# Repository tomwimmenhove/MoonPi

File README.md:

A simple Linux-board with a mini PCIe slot for a 4G LTE module and a 100MBit ethernet port to use as a 4G router.

Specs:
- 100MBit ethernet
- 64MB RAM
- Mini PCIe slot (for an LTE module)
- SD card slot (for firmware)
- SIM card slot
- Allwinner V3S CPU
- 115k2 baud UART console/debugging interface (Optionally over USB)

Thanks to [Dmitry Poskriyakov](https://github.com/balmerdx/AllwinnerV3S_KiCad) for creating the footprints for the used Allwinner V3S CPU.

Multiple kernel versions with working .config files can be found [here](https://github.com/tomwimmenhove/moonpi-linux/).
A U-boot .config is included in [this repository](https://github.com/tomwimmenhove/AllwinnerLTE/blob/main/software/config_notes/uboot.config) and a working version of U-Boot has been forked [here](https://github.com/tomwimmenhove/u-boot).
And finally, ~a working filesystem for the SD-card can be found [here](https://drive.google.com/drive/folders/1GH_1jrhb02dNxiufkJj9f3y94fUZBKtc)~ a working SD-card image with OpenWRT is available [here](https://github.com/tomwimmenhove/MoonPi/blob/main/software/sd_card_image/openwrt.img.gz?raw=true).

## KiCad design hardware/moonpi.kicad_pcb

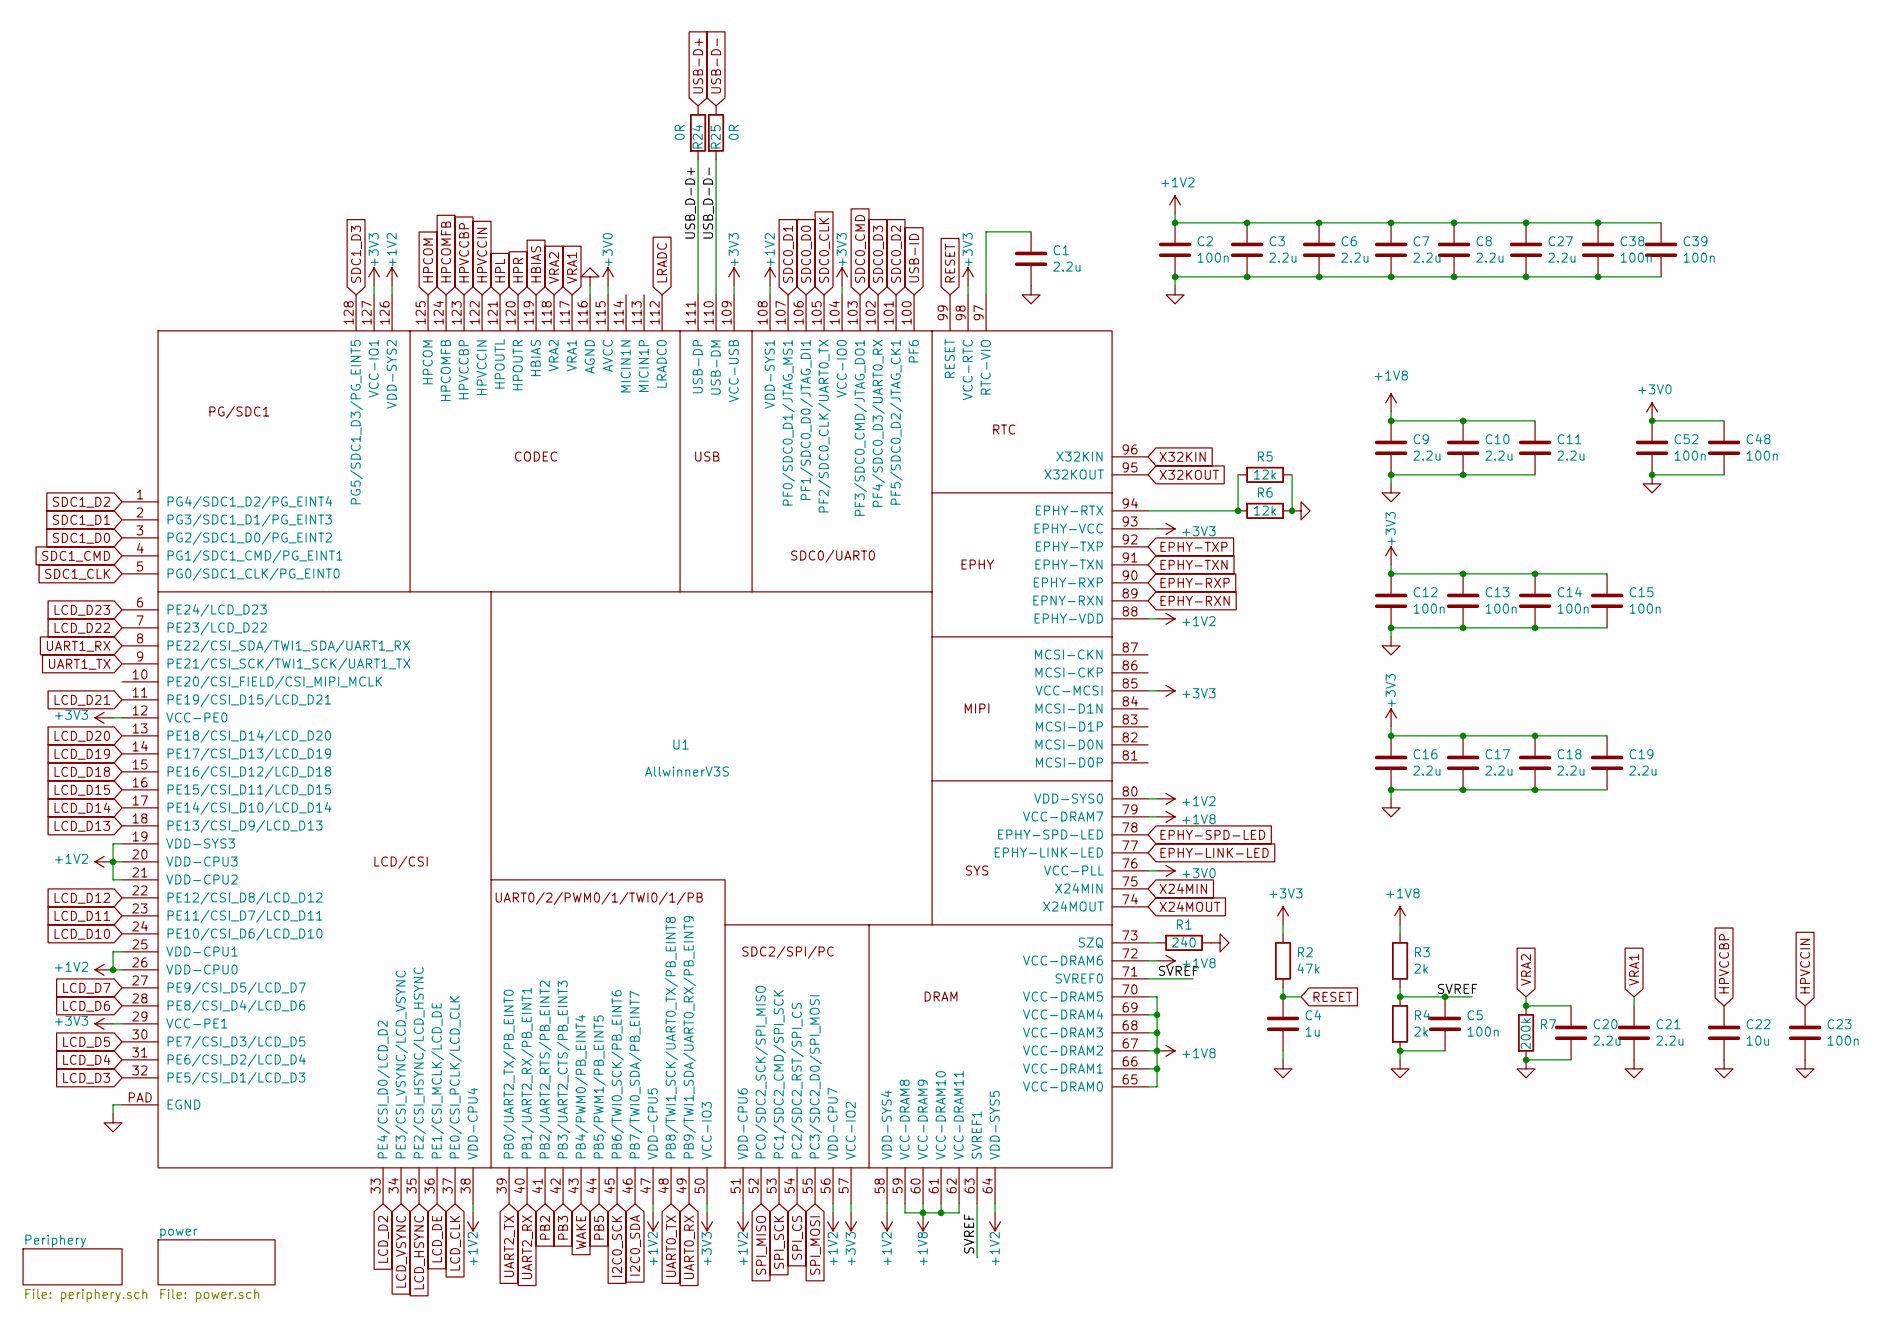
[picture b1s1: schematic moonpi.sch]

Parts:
C1, C3, C6, C7, C8, C9, C10, C11, C16, C17, C18, C19, C20, C21, C27: 2.2u; C_0805_2012Metric
C2, C5, C12, C13, C14, C15, C23, C38, C39, C48, C52: 100n; C_0603_1608Metric
C4: 1u; C_0603_1608Metric
C22: 10u; C_0805_2012Metric
R1: 240; R_0603_1608Metric
R2: 47k; R_0603_1608Metric
R3, R4: 2k; R_0603_1608Metric
R5, R6: 12k; R_0603_1608Metric
R7: 200k; R_0603_1608Metric
R24, R25: 0R; R_0603_1608Metric
U1: AllwinnerV3S; eLQFP-128_14x14mm_P0.4mm

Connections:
+1V2: C2.1, C3.1, C6.1, C7.1, C8.1, C27.1, C38.1, C39.1, U1.19 (VDD-SYS3), U1.20 (VDD-CPU3), U1.21 (VDD-CPU2), U1.25 (VDD-CPU1), U1.26 (VDD-CPU0), U1.38 (VDD-CPU4), U1.47 (VDD-CPU5), U1.51 (VDD-CPU6), U1.56 (VDD-CPU7), U1.58 (VDD-SYS4), U1.64 (VDD-SYS5), U1.80 (VDD-SYS0), U1.88 (EPHY-VDD), U1.108 (VDD-SYS1), U1.126 (VDD-SYS2); also elsewhere on the board
+1V8: C9.1, C10.1, C11.1, R3.1, U1.59 (VCC-DRAM8), U1.60 (VCC-DRAM9), U1.61 (VCC-DRAM10), U1.62 (VCC-DRAM11), U1.65 (VCC-DRAM0), U1.66 (VCC-DRAM1), U1.67 (VCC-DRAM2), U1.68 (VCC-DRAM3), U1.69 (VCC-DRAM4), U1.70 (VCC-DRAM5), U1.72 (VCC-DRAM6), U1.79 (VCC-DRAM7); also elsewhere on the board
+3V0: C48.1, C52.1, U1.76 (VCC-PLL), U1.115 (AVCC); also elsewhere on the board
+3V3: C12.1, C13.1, C14.1, C15.1, C16.1, C17.1, C18.1, C19.1, R2.1, U1.12 (VCC-PE0), U1.29 (VCC-PE1), U1.50 (VCC-IO3), U1.57 (VCC-IO2), U1.85 (VCC-MCSI), U1.93 (EPHY-VCC), U1.98 (VCC-RTC), U1.104 (VCC-IO0), U1.109 (VCC-USB), U1.127 (VCC-IO1); also elsewhere on the board
/SVREF: C5.1, R3.2, R4.1, U1.63 (SVREF1), U1.71 (SVREF0)
/USB_D-D+: R24.2, U1.111 (USB-DP)
/USB_D-D-: R25.2, U1.110 (USB-DM)
EPHY-LINK-LED: U1.77 (EPHY-LINK-LED); also elsewhere on the board
EPHY-RXN: U1.89 (EPNY-RXN); also elsewhere on the board
EPHY-RXP: U1.90 (EPHY-RXP); also elsewhere on the board
EPHY-SPD-LED: U1.78 (EPHY-SPD-LED); also elsewhere on the board
EPHY-TXN: U1.91 (EPHY-TXN); also elsewhere on the board
EPHY-TXP: U1.92 (EPHY-TXP); also elsewhere on the board
GND: C1.2, C2.2, C3.2, C4.2, C5.2, C6.2, C7.2, C8.2, C9.2, C10.2, C11.2, C12.2, C13.2, C14.2, C15.2, C16.2, C17.2, C18.2, C19.2, C20.2, C21.2, C22.2, C23.2, C27.2, C38.2, C39.2, C48.2, C52.2, R1.1, R4.2, R5.1, R6.1, R7.2, U1.116 (AGND), U1.PAD (EGND); also elsewhere on the board
HBIAS: U1.119 (HBIAS)
HPCOM: U1.125 (HPCOM)
HPCOMFB: U1.124 (HPCOMFB)
HPL: U1.121 (HPOUTL)
HPR: U1.120 (HPOUTR)
HPVCCBP: C22.1, U1.123 (HPVCCBP)
HPVCCIN: C23.1, U1.122 (HPVCCIN)
I2C0_SCK: U1.45 (PB6/TWI0_SCK/PB_EINT6)
I2C0_SDA: U1.46 (PB7/TWI0_SDA/PB_EINT7)
LCD_CLK: U1.37 (PE0/CSI_PCLK/LCD_CLK)
LCD_D2: U1.33 (PE4/CSI_D0/LCD_D2)
LCD_D3: U1.32 (PE5/CSI_D1/LCD_D3)
LCD_D4: U1.31 (PE6/CSI_D2/LCD_D4)
LCD_D5: U1.30 (PE7/CSI_D3/LCD_D5)
LCD_D6: U1.28 (PE8/CSI_D4/LCD_D6)
LCD_D7: U1.27 (PE9/CSI_D5/LCD_D7)
LCD_D10: U1.24 (PE10/CSI_D6/LCD_D10)
LCD_D11: U1.23 (PE11/CSI_D7/LCD_D11)
LCD_D12: U1.22 (PE12/CSI_D8/LCD_D12)
LCD_D13: U1.18 (PE13/CSI_D9/LCD_D13)
LCD_D14: U1.17 (PE14/CSI_D10/LCD_D14)
LCD_D15: U1.16 (PE15/CSI_D11/LCD_D15)
LCD_D18: U1.15 (PE16/CSI_D12/LCD_D18)
LCD_D19: U1.14 (PE17/CSI_D13/LCD_D19)
LCD_D20: U1.13 (PE18/CSI_D14/LCD_D20)
LCD_D21: U1.11 (PE19/CSI_D15/LCD_D21)
LCD_D22: U1.7 (PE23/LCD_D22)
LCD_D23: U1.6 (PE24/LCD_D23)
LCD_DE: U1.36 (PE1/CSI_MCLK/LCD_DE)
LCD_HSYNC: U1.35 (PE2/CSI_HSYNC/LCD_HSYNC)
LCD_VSYNC: U1.34 (PE3/CSI_VSYNC/LCD_VSYNC)
LRADC: U1.112 (LRADC0)
unnamed: C1.1, U1.97 (RTC-VIO)
unnamed: R1.2, U1.73 (SZQ)
unnamed: R5.2, R6.2, U1.94 (EPHY-RTX)
PB2: U1.41 (PB2/UART2_RTS/PB_EINT2)
PB3: U1.42 (PB3/UART2_CTS/PB_EINT3)
PB5: U1.44 (PB5/PWM1/PB_EINT5)
RESET: C4.1, R2.2, U1.99 (RESET); also elsewhere on the board
SDC0_CLK: U1.105 (PF2/SDC0_CLK/UART0_TX); also elsewhere on the board
SDC0_CMD: U1.103 (PF3/SDC0_CMD/JTAG_DO1); also elsewhere on the board
SDC0_D0: U1.106 (PF1/SDC0_D0/JTAG_DI1); also elsewhere on the board
SDC0_D1: U1.107 (PF0/SDC0_D1/JTAG_MS1); also elsewhere on the board
SDC0_D2: U1.101 (PF5/SDC0_D2/JTAG_CK1); also elsewhere on the board
SDC0_D3: U1.102 (PF4/SDC0_D3/UART0_RX); also elsewhere on the board
SDC1_CLK: U1.5 (PG0/SDC1_CLK/PG_EINT0); also elsewhere on the board
SDC1_CMD: U1.4 (PG1/SDC1_CMD/PG_EINT1)
SDC1_D0: U1.3 (PG2/SDC1_D0/PG_EINT2)
SDC1_D1: U1.2 (PG3/SDC1_D1/PG_EINT3)
SDC1_D2: U1.1 (PG4/SDC1_D2/PG_EINT4)
SDC1_D3: U1.128 (PG5/SDC1_D3/PG_EINT5)
SPI_CS: U1.54 (PC2/SDC2_RST/SPI_CS); also elsewhere on the board
SPI_MISO: U1.52 (PC0/SDC2_SCK/SPI_MISO); also elsewhere on the board
SPI_MOSI: U1.55 (PC3/SDC2_D0/SPI_MOSI); also elsewhere on the board
SPI_SCK: U1.53 (PC1/SDC2_CMD/SPI_SCK); also elsewhere on the board
UART0_RX: U1.49 (PB9/TWI1_SDA/UART0_RX/PB_EINT9); also elsewhere on the board
UART0_TX: U1.48 (PB8/TWI1_SCK/UART0_TX/PB_EINT8); also elsewhere on the board
UART1_RX: U1.8 (PE22/CSI_SDA/TWI1_SDA/UART1_RX)
UART1_TX: U1.9 (PE21/CSI_SCK/TWI1_SCK/UART1_TX)
UART2_RX: U1.40 (PB1/UART2_RX/PB_EINT1)
UART2_TX: U1.39 (PB0/UART2_TX/PB_EINT0)
USB-D+: R24.1; also elsewhere on the board
USB-D-: R25.1; also elsewhere on the board
USB-ID: U1.100 (PF6); also elsewhere on the board
VRA1: C21.1, U1.117 (VRA1)
VRA2: C20.1, R7.1, U1.118 (VRA2)
WAKE: U1.43 (PB4/PWM0/PB_EINT4); also elsewhere on the board
X24MIN: U1.75 (X24MIN); also elsewhere on the board
X24MOUT: U1.74 (X24MOUT); also elsewhere on the board
X32KIN: U1.96 (X32KIN); also elsewhere on the board
X32KOUT: U1.95 (X32KOUT); also elsewhere on the board

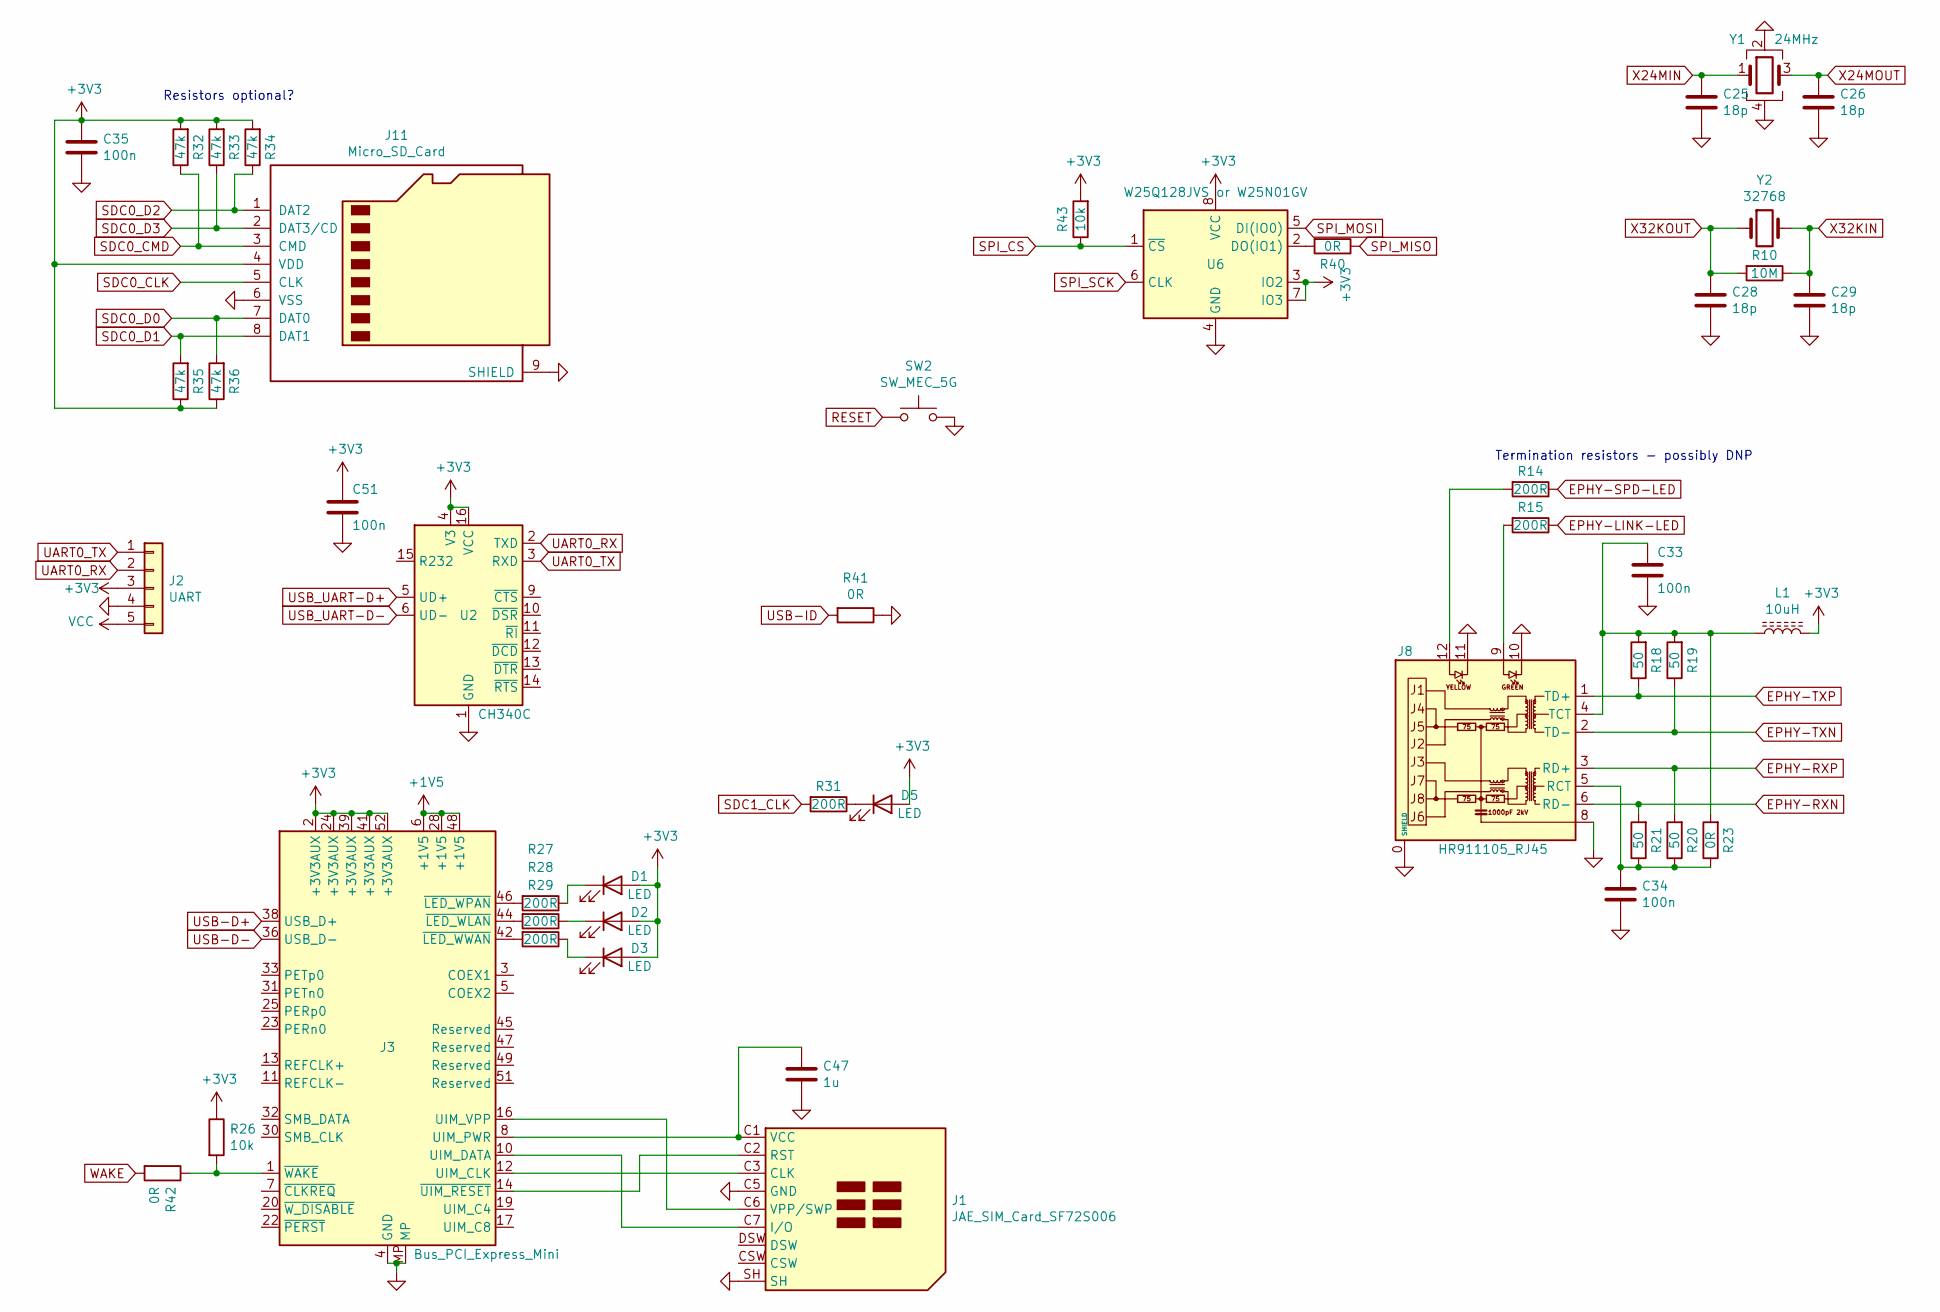
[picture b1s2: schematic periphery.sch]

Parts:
C25, C26, C28, C29: 18p; C_0603_1608Metric
C33, C34, C35, C51: 100n; C_0603_1608Metric
C47: 1u; C_0603_1608Metric
D1, D2, D3, D5: LED; LED_0603_1608Metric
J1: JAE_SIM_Card_SF72S006
J2: UART; PinHeader_1x05_P2.54mm_Vertical
J3: Bus_PCI_Express_Mini; BUS_PCI_Express_Mini_Dual
J8: HR911105_RJ45
J11: Micro_SD_Card; microSD_HC_Wuerth_693072010801
L1: 10uH; L_1206_3216Metric
R10: 10M; R_0805_2012Metric
R14, R15, R27, R28, R29, R31: 200R; R_0603_1608Metric
R18, R19, R20, R21: 50; R_0603_1608Metric
R23, R40, R41, R42: 0R; R_0603_1608Metric
R26, R43: 10k; R_0603_1608Metric
R32, R33, R34, R35, R36: 47k; R_0603_1608Metric
SW2: SW_MEC_5G; SW_SPST_Omron_B3FS-100xP
U2: CH340C; SOIC-16_3.9x9.9mm_P1.27mm
U6: W25Q128JVS or W25N01GV; SOIC-8_5.23x5.23mm_P1.27mm
Y1: 24MHz; Crystal_SMD_3225-4Pin_3.2x2.5mm
Y2: 32768; Crystal_C26-LF_D2.1mm_L6.5mm_Horizontal

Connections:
+1V5: J3.6 (+1V5), J3.28 (+1V5), J3.48 (+1V5); also elsewhere on the board
+3V3: C35.1, C51.1, D1.2 (A), D2.2 (A), D3.2 (A), D5.2 (A), J2.3, J3.2 (+3V3AUX), J3.24 (+3V3AUX), J3.39 (+3V3AUX), J3.41 (+3V3AUX), J3.52 (+3V3AUX), J11.4 (VDD), L1.2, R26.1, R32.2, R33.2, R34.2, R35.1, R36.1, R43.2, U2.4 (V3), U2.16 (VCC), U6.3 (IO2), U6.7 (IO3), U6.8 (VCC); also elsewhere on the board
EPHY-LINK-LED: R15.1; also elsewhere on the board
EPHY-RXN: J8.6 (RD-), R21.2; also elsewhere on the board
EPHY-RXP: J8.3 (RD+), R20.2; also elsewhere on the board
EPHY-SPD-LED: R14.1; also elsewhere on the board
EPHY-TXN: J8.2 (TD-), R19.1; also elsewhere on the board
EPHY-TXP: J8.1 (TD+), R18.1; also elsewhere on the board
GND: C25.2, C26.2, C28.2, C29.2, C33.2, C34.2, C35.2, C47.2, C51.2, J1.C5 (GND), J1.SH, J2.4, J3.4 (GND), J3.9 (GND), J3.15 (GND), J3.18 (GND), J3.21 (GND), J3.26 (GND), J3.27 (GND), J3.29 (GND), J3.34 (GND), J3.35 (GND), J3.37 (GND), J3.40 (GND), J3.43 (GND), J3.50 (GND), J3.MP, J8.0 (SHIELD), J8.8, J8.10, J8.11, J11.6 (VSS), J11.9 (SHIELD), R41.1, SW2.3 (B), SW2.4 (B), U2.1 (GND), U6.4 (GND), Y1.2, Y1.4; also elsewhere on the board
unnamed: C33.1, J8.4 (TCT), L1.1, R18.2, R19.2, R23.2
unnamed: C34.1, J8.5 (RCT), R20.1, R21.1, R23.1
unnamed: C47.1, J1.C1 (VCC), J3.8 (UIM_PWR)
unnamed: D1.1 (K), R27.1
unnamed: D2.1 (K), R28.1
unnamed: D3.1 (K), R29.1
unnamed: D5.1 (K), R31.1
unnamed: J1.C2 (RST), J3.14 (~UIM_RESET)
unnamed: J1.C3 (CLK), J3.12 (UIM_CLK)
unnamed: J1.C6 (VPP/SWP), J3.16 (UIM_VPP)
unnamed: J1.C7 (I/O), J3.10 (UIM_DATA)
unnamed: J3.1 (~WAKE), R26.2, R42.1
unnamed: J3.42 (~LED_WWAN), R29.2
unnamed: J3.44 (~LED_WLAN), R28.2
unnamed: J3.46 (~LED_WPAN), R27.2
unnamed: J8.9, R15.2
unnamed: J8.12, R14.2
unnamed: R40.2, U6.2 (DO(IO1))
RESET: SW2.1 (A), SW2.2 (A); also elsewhere on the board
SDC0_CLK: J11.5 (CLK); also elsewhere on the board
SDC0_CMD: J11.3 (CMD), R32.1; also elsewhere on the board
SDC0_D0: J11.7 (DAT0), R36.2; also elsewhere on the board
SDC0_D1: J11.8 (DAT1), R35.2; also elsewhere on the board
SDC0_D2: J11.1 (DAT2), R34.1; also elsewhere on the board
SDC0_D3: J11.2 (DAT3/CD), R33.1; also elsewhere on the board
SDC1_CLK: R31.2; also elsewhere on the board
SPI_CS: R43.1, U6.1 (~CS); also elsewhere on the board
SPI_MISO: R40.1; also elsewhere on the board
SPI_MOSI: U6.5 (DI(IO0)); also elsewhere on the board
SPI_SCK: U6.6 (CLK); also elsewhere on the board
UART0_RX: J2.2, U2.2 (TXD); also elsewhere on the board
UART0_TX: J2.1, U2.3 (RXD); also elsewhere on the board
USB-D+: J3.38 (USB_D+); also elsewhere on the board
USB-D-: J3.36 (USB_D-); also elsewhere on the board
USB-ID: R41.2; also elsewhere on the board
USB_UART-D+: U2.5 (UD+); also elsewhere on the board
USB_UART-D-: U2.6 (UD-); also elsewhere on the board
VCC: J2.5; also elsewhere on the board
WAKE: R42.2; also elsewhere on the board
X24MIN: C25.1, Y1.1; also elsewhere on the board
X24MOUT: C26.1, Y1.3; also elsewhere on the board
X32KIN: C29.1, R10.1, Y2.2; also elsewhere on the board
X32KOUT: C28.1, R10.2, Y2.1; also elsewhere on the board

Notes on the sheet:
Termination resistors - possibly DNP
Resistors optional?

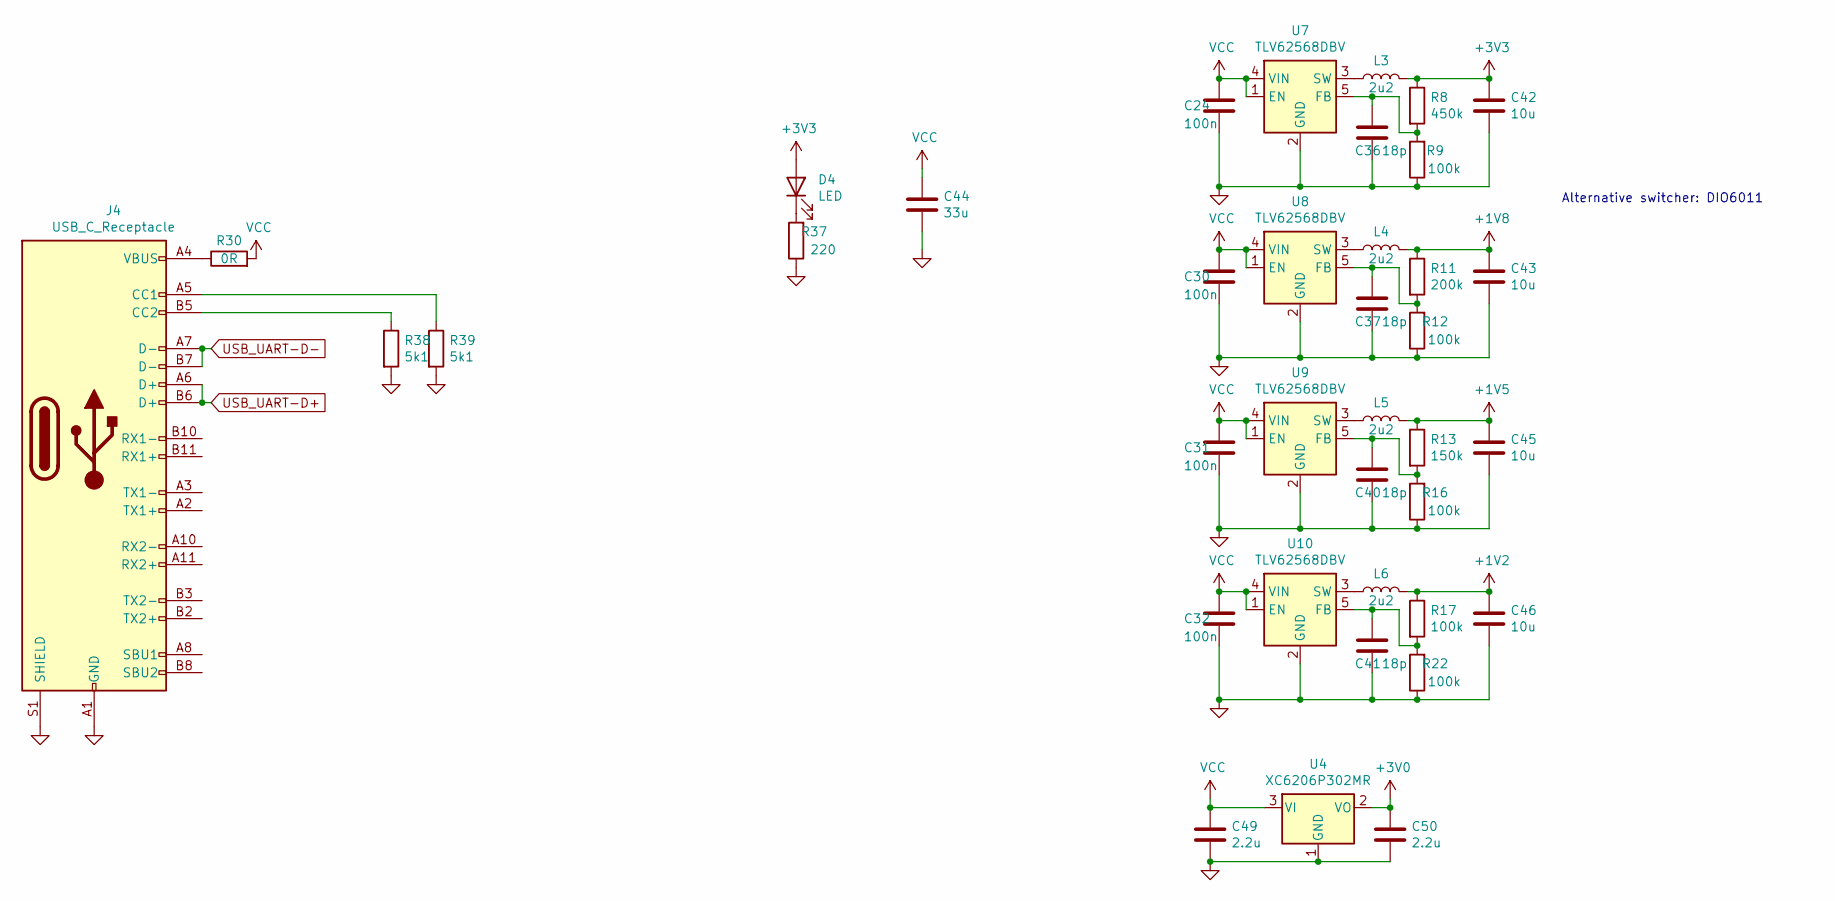
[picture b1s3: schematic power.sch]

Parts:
C24, C30, C31, C32: 100n; C_0603_1608Metric
C36, C37, C40, C41: 18p; C_0603_1608Metric
C42, C43, C45, C46: 10u; C_0805_2012Metric
C44: 33u; C_1206_3216Metric
C49, C50: 2.2u; C_0805_2012Metric
D4: LED; LED_0603_1608Metric
J4: USB_C_Receptacle; USB_C_Receptacle_Amphenol_12401610E4-2A
L3, L4, L5, L6: 2u2; L_TDK_SLF6045
R8: 450k; R_0603_1608Metric
R9, R12, R16, R17, R22: 100k; R_0603_1608Metric
R11: 200k; R_0603_1608Metric
R13: 150k; R_0603_1608Metric
R30: 0R; R_0603_1608Metric
R37: 220; R_0603_1608Metric
R38, R39: 5k1; R_0603_1608Metric
U4: XC6206P302MR; SOT-23
U7, U8, U9, U10: TLV62568DBV; SOT-23-5

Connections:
+1V2: C46.1, L6.2, R17.1; also elsewhere on the board
+1V5: C45.1, L5.2, R13.1; also elsewhere on the board
+1V8: C43.1, L4.2, R11.1; also elsewhere on the board
+3V0: C50.1, U4.2 (VO); also elsewhere on the board
+3V3: C42.1, D4.2 (A), L3.2, R8.1; also elsewhere on the board
GND: C24.2, C30.2, C31.2, C32.2, C36.2, C37.2, C40.2, C41.2, C42.2, C43.2, C44.2, C45.2, C46.2, C49.2, C50.2, J4.A1 (GND), J4.A12 (GND), J4.B1 (GND), J4.B12 (GND), J4.S1 (SHIELD), R9.1, R12.1, R16.1, R22.1, R37.1, R38.2, R39.2, U4.1 (GND), U7.2 (GND), U8.2 (GND), U9.2 (GND), U10.2 (GND); also elsewhere on the board
unnamed: C36.1, R8.2, R9.2, U7.5 (FB)
unnamed: C37.1, R11.2, R12.2, U8.5 (FB)
unnamed: C40.1, R13.2, R16.2, U9.5 (FB)
unnamed: C41.1, R17.2, R22.2, U10.5 (FB)
unnamed: D4.1 (K), R37.2
unnamed: J4.A4 (VBUS), J4.A9 (VBUS), J4.B4 (VBUS), J4.B9 (VBUS), R30.1
unnamed: J4.A5 (CC1), R39.1
unnamed: J4.B5 (CC2), R38.1
unnamed: L3.1, U7.3 (SW)
unnamed: L4.1, U8.3 (SW)
unnamed: L5.1, U9.3 (SW)
unnamed: L6.1, U10.3 (SW)
USB_UART-D+: J4.A6 (D+), J4.B6 (D+); also elsewhere on the board
USB_UART-D-: J4.A7 (D-), J4.B7 (D-); also elsewhere on the board
VCC: C24.1, C30.1, C31.1, C32.1, C44.1, C49.1, R30.2, U4.3 (VI), U7.1 (EN), U7.4 (VIN), U8.1 (EN), U8.4 (VIN), U9.1 (EN), U9.4 (VIN), U10.1 (EN), U10.4 (VIN); also elsewhere on the board

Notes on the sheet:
Alternative switcher: DIO6011

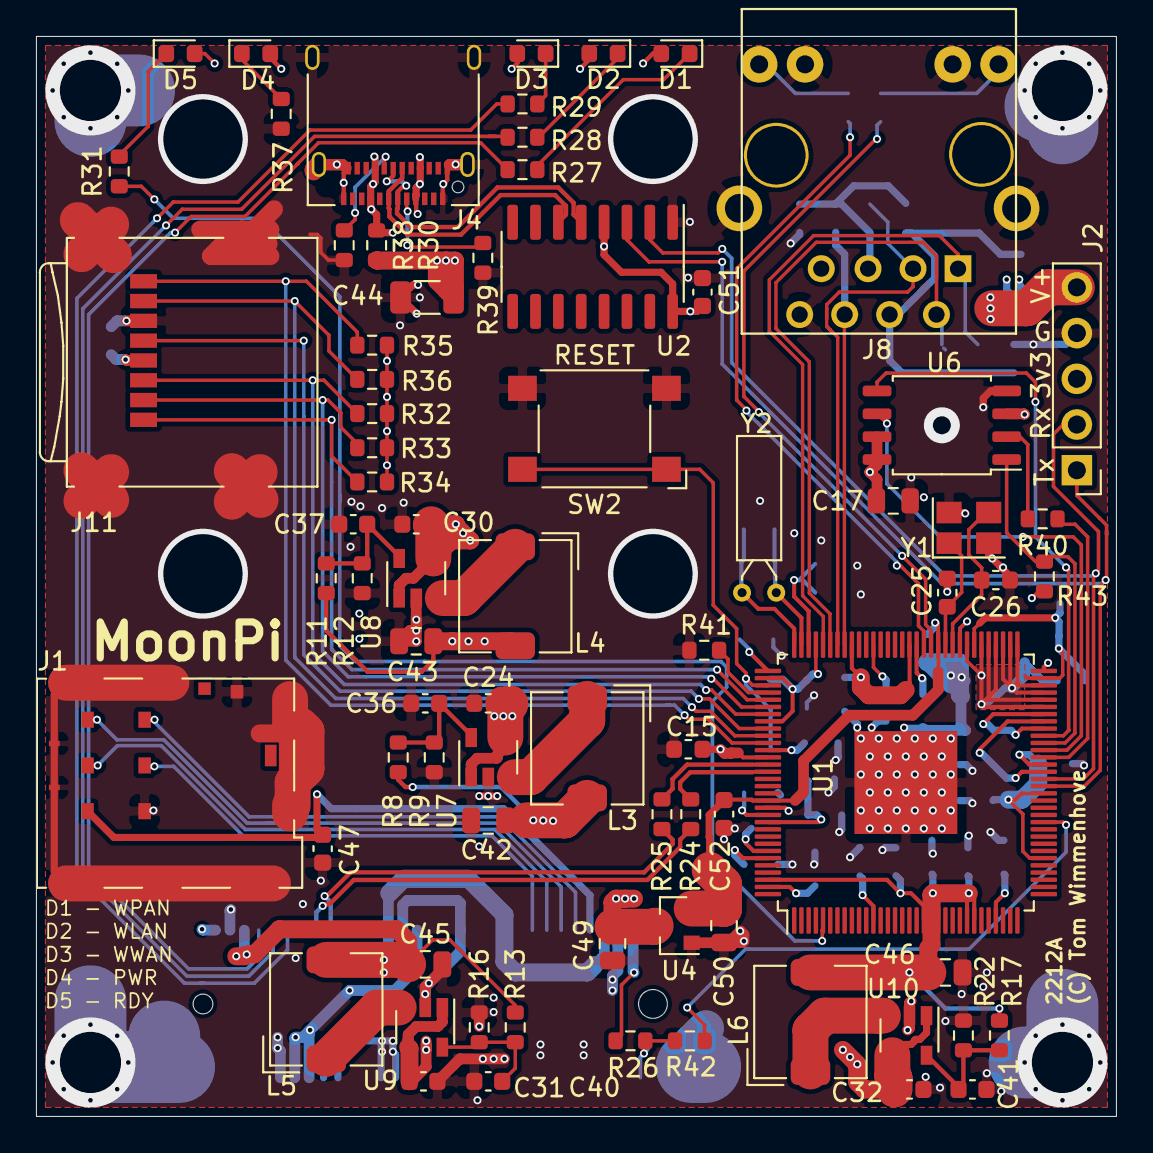
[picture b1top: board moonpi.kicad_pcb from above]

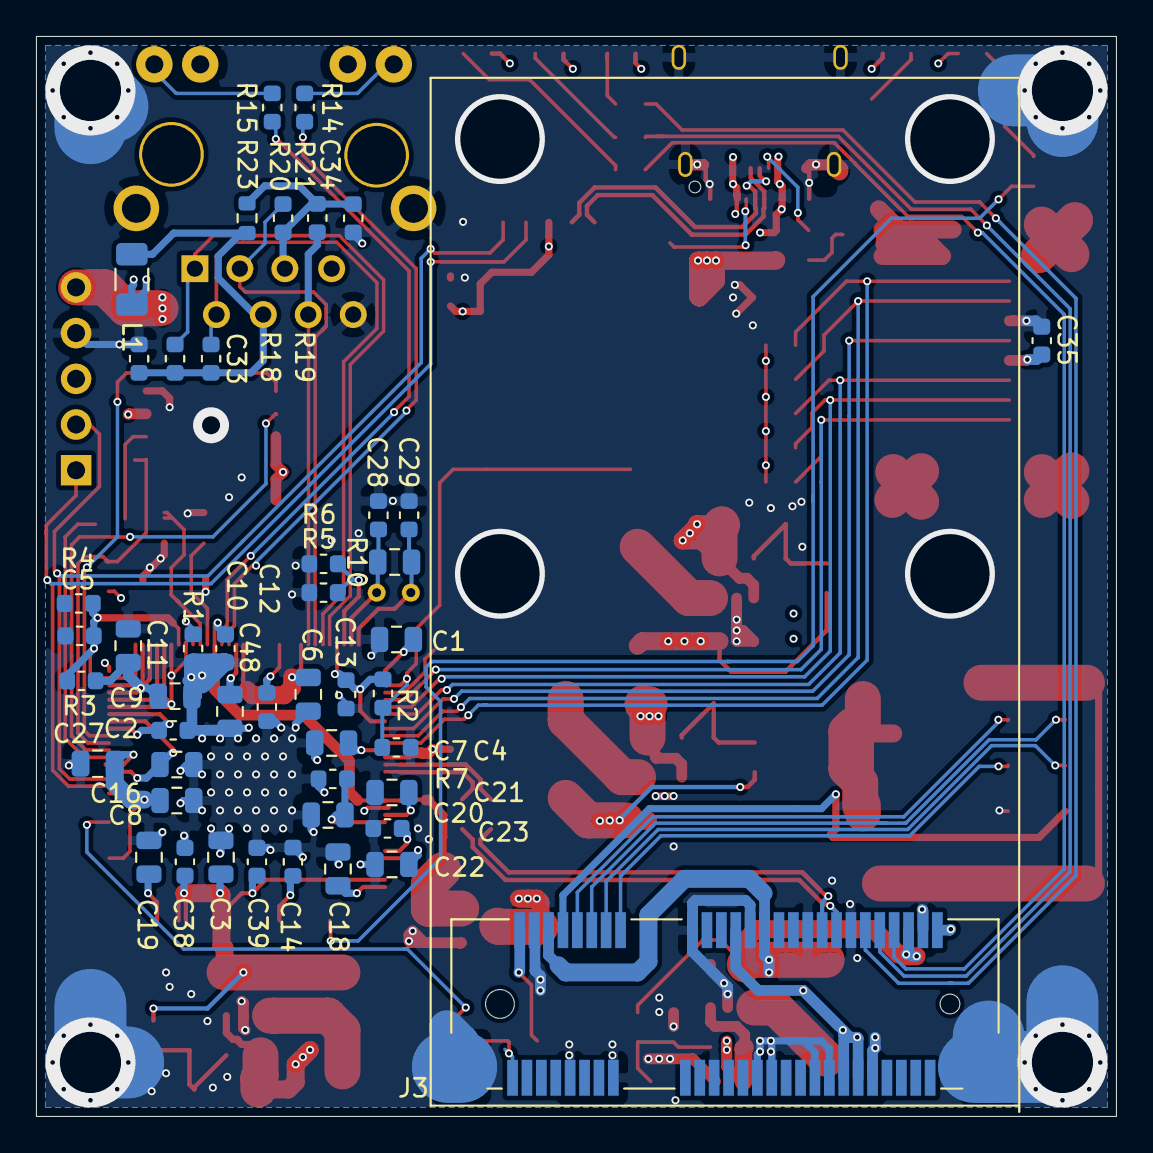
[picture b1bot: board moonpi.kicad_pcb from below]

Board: 4 copper layers, 60.0 x 60.0 mm, 122 parts (47 on the bottom side), 77 nets.

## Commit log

2022-02-12 Some routing done
2022-02-13 More routing. CPU power routed. USB li-ion charging added
2022-02-14 Power routing done
2022-02-15 backup
2022-02-15 Routing done?!
2022-02-16 Fixed refdes placements
2022-02-18 Small touch-ups
2022-02-20 Added USB UART
2022-02-21 Small updates
2022-02-21 Added open hardware logo file
2022-02-21 Removed FEL button
2022-02-23 Removed USB series resistors on mPCIe side
2022-02-23 Fixed DRC
2022-02-24 Added LTE conneciton scripts
2022-03-03 Rotated SIM
2022-03-03 0R between VBus and VCC
2022-03-03 Added some nonsense
2022-03-06 Added an "RDY" LED
2022-03-06 Changed mPCIe mounting holes for PCB inserts: https://www.farnell.com/cad/2720308.pdf (length may vary
2022-03-06 Removed mask and added vias around mounting pads
2022-03-06 Better mechanical support on GND pads for mPCIe conn
2022-03-07 Minor touch-ups
2022-03-11 Added notes and references to working kernel with ethernet and usb
2022-03-11 Added simple helper for network testing (masquerade)
2022-03-12 Updated kernel config to allow NAT
2022-03-12 Added 0R for USB_ID pin + Moved OK LED to licheePi default GPIO
2022-03-13 Added T-PAD below NAND Flash
2022-03-13 Some routingnitpicking
2022-03-13 Kernel config: Added TUN module, ethernet as module and model serial ports
2022-03-13 Translated Russian comments
2022-03-13 Actually comitted the translation
2022-03-13 Replaced SD card slot with Wurth 693072010801
2022-03-13 Forgot some GND vias
2022-03-14 Some routing improvements
2022-03-16 Added config notes for uboot
2022-03-18 Added bridging to kernel config
2022-03-19 Removed SMP
2022-03-19 Some more kernel trimming
2022-03-19 Changed kernel name
2022-03-20 More trimming
2022-03-21 Slightly more trimming?
2022-03-21 Move Y1 to top-layer
2022-03-21 Improved spacing
2022-03-21 Minor layout changes
2022-03-21 Ready for JLCPCB
2022-03-22 Update network helper script
2022-03-24 Include more modules + IPV6 support
2022-03-30 Updated notes
2022-04-03 Fixed filenames
2022-04-03 Fixed filename verioning
2022-04-03 Added readme
2022-04-03 Added pictures
2022-04-16 Added 3D model for case
2022-04-23 Changed USB series termination resistors values to zero-ohm
2022-04-23 3D case latch and other improvements
2022-04-26 Small 3D model fixes
2022-04-26 Thicker USB wall
2022-05-02 3D case improvements
2022-05-02 Added OpenWRT sd-card image
2022-05-03 Moved file
2022-05-03 Updated network helper IP
2022-05-03 Added cased picture
2022-05-03 Update README.md
    Added picture of router in case.
2022-05-03 Update README.md
    Raw link to SD-card image
2022-05-15 FIX: Added pull-up on SPI /CS
